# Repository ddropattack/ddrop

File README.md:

# DDRop: Active Memory Interposer Attacks on Confidential VMs by Dropping DDR5 Writes

This repository contains the hardware designs, firmware, host evaluation tools, and attack proof-of-concepts for [**DDRop**](https://ddropattack.eu/ddrop.pdf).

* **Authors:** Jesse De Meulemeester (KU Leuven), Stefan Gloor (ETH Zurich), Patrick Jattke (ETH Zurich), Daniel Moghimi (Google), David Oswald (Durham University), Martin Thompson (Durham University & ZF Automotive UK Ltd), Kaveh Razavi (ETH Zurich), Ingrid Verbauwhede (KU Leuven), and Jo Van Bulck (KU Leuven)

---

## Overview

Modern Trusted Execution Environments (TEEs) such as Intel TDX, Intel Scalable SGX, and AMD SEV-SNP rely on memory encryption to protect enclaves and confidential VMs from an untrusted hypervisor or cloud operator. However, to maintain memory performance, scalable cloud TEEs omit cryptographic freshness guarantees.

DDRop demonstrates active physical interposition attacks on DDR5 at native bus speeds using a custom low-cost DDR5 RDIMM interposer. By injecting parity errors on DDR5 command/address lines, the interposer silently discards cache line writebacks (dropping writes) or swaps chip selects. This repository contains the full materials to inspect, build, and evaluate the interposer hardware, controller firmware, host primitives, and confidential VM attacks.

---

## Repository Structure & Paper Mapping

The contents of this repository correspond directly to the sections of the paper:

| Directory | Paper Section | Description |
|:---|:---|:---|
| [`rdimm-interposer/`](./rdimm-interposer/) | §4.1 | DDR5 RDIMM interposer PCB designs |
| [`rdimm-injection-controller/`](./rdimm-injection-controller/) | §4.1 | Microcontroller injection board designs |
| [`rdimm-injection-controller-firmware/`](./rdimm-injection-controller-firmware/) | §4.1 | Teensy 4.1 firmware & Python control scripts |
| [`host-evaluation/`](./host-evaluation/) | §4.2 | Bare-metal host evaluation of DDRop primitives | 
| [`sev-attacks/`](./sev-attacks/) | §5.1, §5.2.1 | Attacks on AMD SEV-SNP |
| [`sgx-attacks/`](./sgx-attacks/) | §5.1 | Attacks on Intel Scalable SGX | 
| [`tdx-attacks/`](./tdx-attacks/) | §5.1, §5.2.1, §5.2.2, §6 | Attacks on Intel TDX | 

Demonstration videos recorded during physical attack execution are available in the respective directories:
* AMD SEV-SNP write drop: [`sev-attacks/drop-write/sev-drop-write.png`](./sev-attacks/drop-write/sev-drop-write.png)
* AMD SEV-SNP `SNP_PAGE_MOVE` exploit: [`sev-attacks/page-move/sev-page-move.webm`](./sev-attacks/page-move/sev-page-move.webm)
* Intel Scalable SGX write drop: [`sgx-attacks/drop-write/sgx-drop-write.mp4`](./sgx-attacks/drop-write/sgx-drop-write.mp4)
* Intel TDX page relocation: [`tdx-attacks/page-relocate/tdx-page-relocate.webm`](./tdx-attacks/page-relocate/tdx-page-relocate.webm)
* Intel TDX debug bit flip: [`tdx-attacks/sept-injection/tdcs-poc.mp4`](./tdx-attacks/sept-injection/tdcs-poc.mp4)

---

## Getting Started

### Hardware and Software Requirements

#### Software & Build Environment
* Linux x86_64 system
* GCC (supporting C11 / C++17) and Make
* Python 3.8+ with `requirements.txt` packages installed
* [KiCad](https://www.kicad.org/) (v9.0 or later) to view PCB schematics and layouts
* [Arduino IDE](https://www.arduino.cc/) or `teensy_loader_cli` with Teensyduino support (for compiling and flashing the controller firmware)

#### Physical Experiment Requirements
End-to-end physical replication of the attacks requires:
1. The manufactured **DDR5 RDIMM Interposer** and **Injection Controller** boards (design files in `rdimm-interposer/` and `rdimm-injection-controller/`).
2. A **Teensy 4.1** microcontroller board connected to the injection controller.
3. Server hardware with DDR5 RDIMM slots supporting the target TEE:
   * **Intel TDX**: 5th/6th Gen Intel Xeon Scalable processor with TDX enabled.
   * **AMD SEV-SNP**: 4th/5th/6th Gen AMD EPYC processor with SEV-SNP enabled.
   * **Intel Scalable SGX**: 4th/5th/6th Gen Intel Xeon Scalable processor with SGX enabled.

When physical interposer hardware is not available, the software components and attack binaries can still be compiled locally, and their execution flow can be cross-referenced with the provided screencasts.

### Building the Artifacts

You can verify and build all host evaluation tools and attack PoCs from the repository root:

```bash
make all
```

This command automatically builds the dependencies and produces:
* **Host evaluation primitives** (`host-evaluation/drop-write`, `swap-ranks`, `drop-read`)
* **AMD SEV-SNP attack binaries** (`sev-attacks/drop-write`, `page-move`, `movepage`)
* **Intel TDX attack binaries** (`tdx-attacks/drop-write`, `page-relocate`, `attacker-td`, `victim-td`)

To remove all built binaries and object files:
```bash
make clean
```

> [!NOTE]
> Building Intel Scalable SGX enclaves (`sgx-attacks/`) requires the Intel SGX SDK and SGX-Step with `LIBSGXSTEP_DIR` set (see [`sgx-attacks/README.md`](sgx-attacks/README.md)). The microcontroller firmware can be compiled with `make firmware` (see [`rdimm-injection-controller-firmware/README.md`](rdimm-injection-controller-firmware/README.md)).

---

## Detailed Instructions

Refer to the individual README files in each folder for specific execution steps, kernel patch instructions, and command-line parameters:
* [`rdimm-interposer/README.md`](rdimm-interposer/README.md): Interposer specifications, stackup, and modification instructions.
* [`rdimm-injection-controller/README.md`](rdimm-injection-controller/README.md): Controller board hardware and assembly.
* [`rdimm-injection-controller-firmware/README.md`](rdimm-injection-controller-firmware/README.md): Firmware flashing and control API.
* [`host-evaluation/README.md`](host-evaluation/README.md): Running host-level write drop, read drop, and rank swapping primitives.
* [`sev-attacks/README.md`](sev-attacks/README.md): AMD SEV-SNP setup and attack steps.
* [`sgx-attacks/README.md`](sgx-attacks/README.md): Intel Scalable SGX driver patches and enclave evaluation.
* [`tdx-attacks/README.md`](tdx-attacks/README.md): Intel TDX kernel/TDXplore patches, page relocation, and SEPT injection attacks.

---

## Citation

If you reference or build upon this work, please cite the paper:

```bibtex
@inproceedings{ddrop26,
  title     = {{DDRop}: Active Memory Interposer Attacks on Confidential {VMs} by Dropping {DDR5} Writes},
  author    = {De Meulemeester, Jesse and Gloor, Stefan and Jattke, Patrick and Moghimi, Daniel and Oswald, David and Thompson, Martin and Razavi, Kaveh and Verbauwhede, Ingrid and Van Bulck, Jo},
  booktitle = {Proceedings of the 2026 {ACM} {SIGSAC} Conference on Computer and Communications Security ({CCS} '26)},
  publisher = {ACM},
  year      = 2026,
}
```

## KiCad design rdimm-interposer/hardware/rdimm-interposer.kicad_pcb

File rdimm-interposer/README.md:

# RDIMM Interposer

This is an RDIMM variant of the [REFault](https://github.com/comsec-group/refault) [DDR5 fault injection interposer](https://github.com/refault-artifacts/fault-injection-interposer).
Like REFault, the RDIMM interposer supports faulting command/address lines (`CA0-6`).
Additionally, the two chip selects (`CS0` and `CS1`) can be swapped.
Unlike UDIMM, RDIMM has `ALERT_n` and `PAR_A` signals.
`ALERT_n` can be disconnected, leading to a suppressed signal.

With a simple hardware modification, it is also possible to entirely disconnect the `CS0` signal at will (without swapping it with `CS1`).

1. Remove the switch for `CS1` (U19).
1. Cut the trace `CS1_A_n_HOST`
1. Connect `CS1_A_n_HOST` to `CS1_A_n_DIMM`
1. Connect A1 (Pin 1) of U19 (which is connected to B1, Pin 3, of U18) to 1.1V.

Now, `CS1` should be permanently connected, while `CS0` is either connected normally, or the DIMM side is connected to +1.1V, depending on the state of `CS_SWAP`.
Even for single-rank DIMMs, `CS1` still needs to be connected for memory training.
This modification should be integrated into the next PCB revision.

The flat-flex connector is electrically compatible to the [REFault injection controller](https://github.com/refault-artifacts/injection-controller),
so only a firmware change is necessary.

## Mechanical
The mechanical dimensions of DDR5 UDIMMs and RDIMMs are specified in [JEDEC MO-329](https://www.jedec.org/system/files/docs/MO-329I.pdf).
Both variants are the same size and both of them have 288 pins.
They only differ by notch position.
See [docs/drawing.pdf](docs/drawing.pdf) for a mechanical drawing.

## PCB
The PCB was designed using KiCAD v9.0.1.

### Stackup
It has 6 layers and is impedance-controlled, as specified by
`JEDEC RDIMM Raw Card C Annex (JESD305-R8-RCC) v2.0`.
See [docs/drawing.pdf](docs/drawing.pdf) for detailed stackup and trace impedance information.

### Order Information
The PCB was ordered at JLCPCB.

| Option | Value |
|--------|-------|
|Base Material| FR-4|
|Layers| 6|
|Dimension| 133.35 mm* 22.51 mm|
|Product Type| Industrial/Consumer electronics|
|Different Design| 1|
|Delivery Format| Single PCB|
|PCB Thickness| 1.2mm|
|Specify Stackup| yes JLC06121H-1080|
|PCB Color| Green|
|Silkscreen| White|
|Material Type| FR-4 TG155|
|Via Covering| Epoxy Filled & Capped|
|Surface Finish| ENIG|
|Gold Thickness| 2U"|
|Deburring/Edge rounding| Yes|
|Outer Copper Weight| 1 oz|
|Inner Copper Weight| 0.5 oz|
|Gold Fingers| No|
|Electrical Test| Flying Probe Fully Test|
|Castellated Holes| no|
|Press-Fit Hole| No|
|Edge Plating| No|
|Mark on PCB| Order Number|
|Blind Slot| No|
|Min via hole size/diameter| 0.15mm/(0.25/0.3mm)|
|4-Wire Kelvin Test| Yes|
|Paper between PCBs| No|
|Appearance Quality| IPC Class 2 Standard|
|Confirm Production file| No|
|Silkscreen Technology| Ink-jet/Screen Printing Silkscreen|
|Package Box| With JLCPCB logo|
|Inspection Report| No|
|Board Outline Tolerance| ±0.2mm(Regular)|

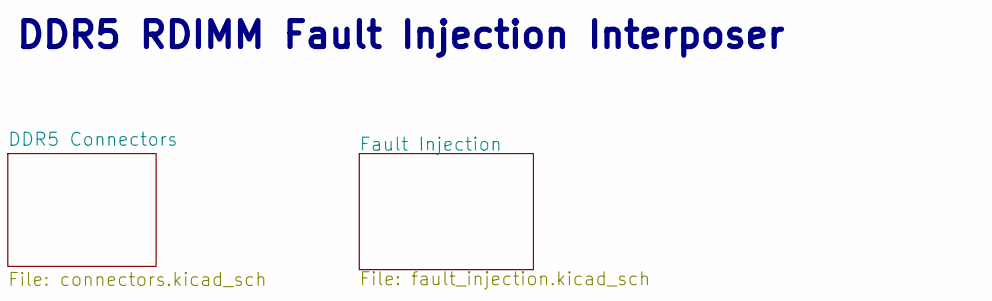
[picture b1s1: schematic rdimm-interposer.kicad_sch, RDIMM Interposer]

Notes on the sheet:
DDR5 RDIMM Fault Injection Interposer

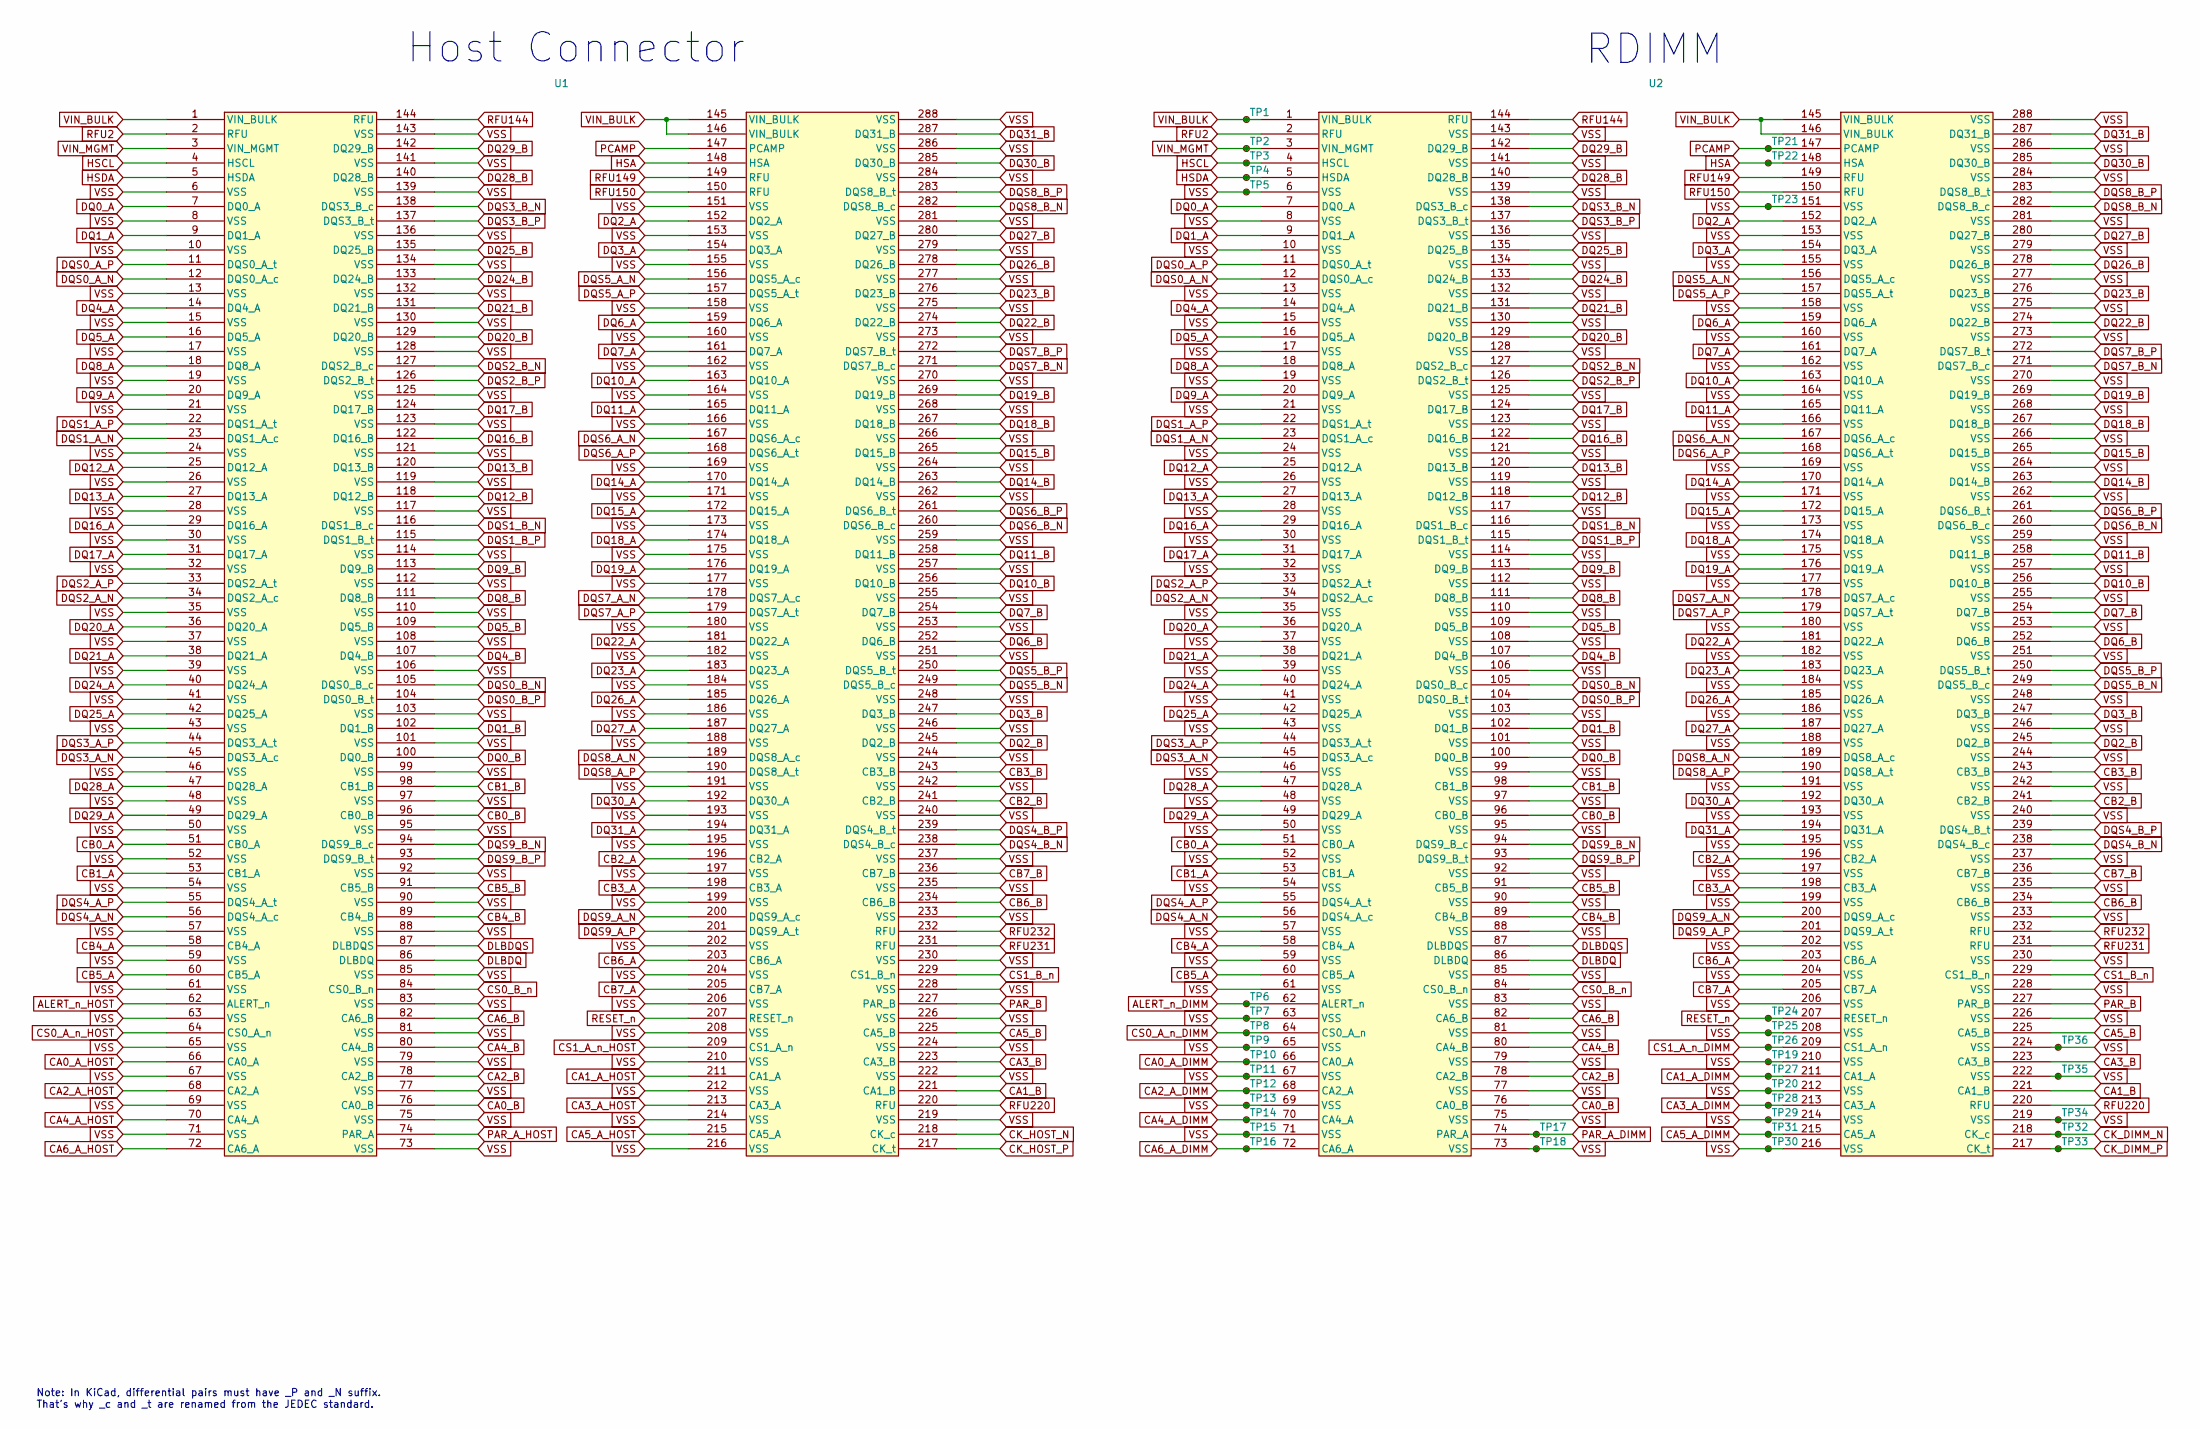
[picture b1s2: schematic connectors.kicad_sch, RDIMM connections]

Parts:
TP1: VIN_BULK; testpoint_small
TP2: VIN_MGMT; testpoint
TP3: HSCL; testpoint
TP4: HSDA; testpoint
TP5, TP7, TP9, TP11, TP13, TP15, TP18, TP19, TP20, TP25, TP29, TP30, TP34, TP35, TP36: VSS; testpoint_small
TP6: ALERT; testpoint
TP8: CS0; testpoint
TP10: CA0; testpoint
TP12: CA2; testpoint
TP14: CA4; testpoint
TP16: CA6; testpoint
TP17: PAR; testpoint
TP21: PCAMP; testpoint
TP22: HSA; testpoint
TP23: TestPoint_Small; testpoint_small
TP24: RESET; testpoint
TP26: CS1; testpoint
TP27: CA1; testpoint
TP28: CA3; testpoint
TP31: CA5; testpoint
TP32: CK_c; testpoint
TP33: CK_t; testpoint
U1: ddr5_edge_connector
U2: ddr5_bottom_conn_double

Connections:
ALERT_n_DIMM: TP6.1, U2.62 (ALERT_n); also elsewhere on the board
ALERT_n_HOST: U1.62 (ALERT_n); also elsewhere on the board
CA0_A_DIMM: TP10.1, U2.66 (CA0_A); also elsewhere on the board
CA0_A_HOST: U1.66 (CA0_A); also elsewhere on the board
CA0_B: U1.76 (CA0_B), U2.76 (CA0_B)
CA1_A_DIMM: TP27.1, U2.211 (CA1_A); also elsewhere on the board
CA1_A_HOST: U1.211 (CA1_A); also elsewhere on the board
CA1_B: U1.221 (CA1_B), U2.221 (CA1_B)
CA2_A_DIMM: TP12.1, U2.68 (CA2_A); also elsewhere on the board
CA2_A_HOST: U1.68 (CA2_A); also elsewhere on the board
CA2_B: U1.78 (CA2_B), U2.78 (CA2_B)
CA3_A_DIMM: TP28.1, U2.213 (CA3_A); also elsewhere on the board
CA3_A_HOST: U1.213 (CA3_A); also elsewhere on the board
CA3_B: U1.223 (CA3_B), U2.223 (CA3_B)
CA4_A_DIMM: TP14.1, U2.70 (CA4_A); also elsewhere on the board
CA4_A_HOST: U1.70 (CA4_A); also elsewhere on the board
CA4_B: U1.80 (CA4_B), U2.80 (CA4_B)
CA5_A_DIMM: TP31.1, U2.215 (CA5_A); also elsewhere on the board
CA5_A_HOST: U1.215 (CA5_A); also elsewhere on the board
CA5_B: U1.225 (CA5_B), U2.225 (CA5_B)
CA6_A_DIMM: TP16.1, U2.72 (CA6_A); also elsewhere on the board
CA6_A_HOST: U1.72 (CA6_A); also elsewhere on the board
CA6_B: U1.82 (CA6_B), U2.82 (CA6_B)
CB0_A: U1.51 (CB0_A), U2.51 (CB0_A)
CB0_B: U1.96 (CB0_B), U2.96 (CB0_B)
CB1_A: U1.53 (CB1_A), U2.53 (CB1_A)
CB1_B: U1.98 (CB1_B), U2.98 (CB1_B)
CB2_A: U1.196 (CB2_A), U2.196 (CB2_A)
CB2_B: U1.241 (CB2_B), U2.241 (CB2_B)
CB3_A: U1.198 (CB3_A), U2.198 (CB3_A)
CB3_B: U1.243 (CB3_B), U2.243 (CB3_B)
CB4_A: U1.58 (CB4_A), U2.58 (CB4_A)
CB4_B: U1.89 (CB4_B), U2.89 (CB4_B)
CB5_A: U1.60 (CB5_A), U2.60 (CB5_A)
CB5_B: U1.91 (CB5_B), U2.91 (CB5_B)
CB6_A: U1.203 (CB6_A), U2.203 (CB6_A)
CB6_B: U1.234 (CB6_B), U2.234 (CB6_B)
CB7_A: U1.205 (CB7_A), U2.205 (CB7_A)
CB7_B: U1.236 (CB7_B), U2.236 (CB7_B)
CK_DIMM_N: TP32.1, U2.218 (CK_c); also elsewhere on the board
CK_DIMM_P: TP33.1, U2.217 (CK_t); also elsewhere on the board
CK_HOST_N: U1.218 (CK_c); also elsewhere on the board
CK_HOST_P: U1.217 (CK_t); also elsewhere on the board
CS0_A_n_DIMM: TP8.1, U2.64 (CS0_A_n); also elsewhere on the board
CS0_A_n_HOST: U1.64 (CS0_A_n); also elsewhere on the board
CS0_B_n: U1.84 (CS0_B_n), U2.84 (CS0_B_n)
CS1_A_n_DIMM: TP26.1, U2.209 (CS1_A_n); also elsewhere on the board
CS1_A_n_HOST: U1.209 (CS1_A_n); also elsewhere on the board
CS1_B_n: U1.229 (CS1_B_n), U2.229 (CS1_B_n)
DLBDQ: U1.86 (DLBDQ), U2.86 (DLBDQ)
DLBDQS: U1.87 (DLBDQS), U2.87 (DLBDQS)
DQ0_A: U1.7 (DQ0_A), U2.7 (DQ0_A)
DQ0_B: U1.100 (DQ0_B), U2.100 (DQ0_B)
DQ1_A: U1.9 (DQ1_A), U2.9 (DQ1_A)
DQ1_B: U1.102 (DQ1_B), U2.102 (DQ1_B)
DQ2_A: U1.152 (DQ2_A), U2.152 (DQ2_A)
DQ2_B: U1.245 (DQ2_B), U2.245 (DQ2_B)
DQ3_A: U1.154 (DQ3_A), U2.154 (DQ3_A)
DQ3_B: U1.247 (DQ3_B), U2.247 (DQ3_B)
DQ4_A: U1.14 (DQ4_A), U2.14 (DQ4_A)
DQ4_B: U1.107 (DQ4_B), U2.107 (DQ4_B)
DQ5_A: U1.16 (DQ5_A), U2.16 (DQ5_A)
DQ5_B: U1.109 (DQ5_B), U2.109 (DQ5_B)
DQ6_A: U1.159 (DQ6_A), U2.159 (DQ6_A)
DQ6_B: U1.252 (DQ6_B), U2.252 (DQ6_B)
DQ7_A: U1.161 (DQ7_A), U2.161 (DQ7_A)
DQ7_B: U1.254 (DQ7_B), U2.254 (DQ7_B)
DQ8_A: U1.18 (DQ8_A), U2.18 (DQ8_A)
DQ8_B: U1.111 (DQ8_B), U2.111 (DQ8_B)
DQ9_A: U1.20 (DQ9_A), U2.20 (DQ9_A)
DQ9_B: U1.113 (DQ9_B), U2.113 (DQ9_B)
DQ10_A: U1.163 (DQ10_A), U2.163 (DQ10_A)
DQ10_B: U1.256 (DQ10_B), U2.256 (DQ10_B)
DQ11_A: U1.165 (DQ11_A), U2.165 (DQ11_A)
DQ11_B: U1.258 (DQ11_B), U2.258 (DQ11_B)
DQ12_A: U1.25 (DQ12_A), U2.25 (DQ12_A)
DQ12_B: U1.118 (DQ12_B), U2.118 (DQ12_B)
DQ13_A: U1.27 (DQ13_A), U2.27 (DQ13_A)
DQ13_B: U1.120 (DQ13_B), U2.120 (DQ13_B)
DQ14_A: U1.170 (DQ14_A), U2.170 (DQ14_A)
DQ14_B: U1.263 (DQ14_B), U2.263 (DQ14_B)
DQ15_A: U1.172 (DQ15_A), U2.172 (DQ15_A)
DQ15_B: U1.265 (DQ15_B), U2.265 (DQ15_B)
DQ16_A: U1.29 (DQ16_A), U2.29 (DQ16_A)
DQ16_B: U1.122 (DQ16_B), U2.122 (DQ16_B)
DQ17_A: U1.31 (DQ17_A), U2.31 (DQ17_A)
DQ17_B: U1.124 (DQ17_B), U2.124 (DQ17_B)
DQ18_A: U1.174 (DQ18_A), U2.174 (DQ18_A)
DQ18_B: U1.267 (DQ18_B), U2.267 (DQ18_B)
DQ19_A: U1.176 (DQ19_A), U2.176 (DQ19_A)
DQ19_B: U1.269 (DQ19_B), U2.269 (DQ19_B)
DQ20_A: U1.36 (DQ20_A), U2.36 (DQ20_A)
DQ20_B: U1.129 (DQ20_B), U2.129 (DQ20_B)
DQ21_A: U1.38 (DQ21_A), U2.38 (DQ21_A)
DQ21_B: U1.131 (DQ21_B), U2.131 (DQ21_B)
DQ22_A: U1.181 (DQ22_A), U2.181 (DQ22_A)
DQ22_B: U1.274 (DQ22_B), U2.274 (DQ22_B)
DQ23_A: U1.183 (DQ23_A), U2.183 (DQ23_A)
DQ23_B: U1.276 (DQ23_B), U2.276 (DQ23_B)
DQ24_A: U1.40 (DQ24_A), U2.40 (DQ24_A)
DQ24_B: U1.133 (DQ24_B), U2.133 (DQ24_B)
DQ25_A: U1.42 (DQ25_A), U2.42 (DQ25_A)
DQ25_B: U1.135 (DQ25_B), U2.135 (DQ25_B)
DQ26_A: U1.185 (DQ26_A), U2.185 (DQ26_A)
DQ26_B: U1.278 (DQ26_B), U2.278 (DQ26_B)
DQ27_A: U1.187 (DQ27_A), U2.187 (DQ27_A)
DQ27_B: U1.280 (DQ27_B), U2.280 (DQ27_B)
DQ28_A: U1.47 (DQ28_A), U2.47 (DQ28_A)
DQ28_B: U1.140 (DQ28_B), U2.140 (DQ28_B)
DQ29_A: U1.49 (DQ29_A), U2.49 (DQ29_A)
DQ29_B: U1.142 (DQ29_B), U2.142 (DQ29_B)
DQ30_A: U1.192 (DQ30_A), U2.192 (DQ30_A)
DQ30_B: U1.285 (DQ30_B), U2.285 (DQ30_B)
DQ31_A: U1.194 (DQ31_A), U2.194 (DQ31_A)
DQ31_B: U1.287 (DQ31_B), U2.287 (DQ31_B)
DQS0_A_N: U1.12 (DQS0_A_c), U2.12 (DQS0_A_c)
DQS0_A_P: U1.11 (DQS0_A_t), U2.11 (DQS0_A_t)
DQS0_B_N: U1.105 (DQS0_B_c), U2.105 (DQS0_B_c)
DQS0_B_P: U1.104 (DQS0_B_t), U2.104 (DQS0_B_t)
DQS1_A_N: U1.23 (DQS1_A_c), U2.23 (DQS1_A_c)
DQS1_A_P: U1.22 (DQS1_A_t), U2.22 (DQS1_A_t)
DQS1_B_N: U1.116 (DQS1_B_c), U2.116 (DQS1_B_c)
DQS1_B_P: U1.115 (DQS1_B_t), U2.115 (DQS1_B_t)
DQS2_A_N: U1.34 (DQS2_A_c), U2.34 (DQS2_A_c)
DQS2_A_P: U1.33 (DQS2_A_t), U2.33 (DQS2_A_t)
DQS2_B_N: U1.127 (DQS2_B_c), U2.127 (DQS2_B_c)
DQS2_B_P: U1.126 (DQS2_B_t), U2.126 (DQS2_B_t)
DQS3_A_N: U1.45 (DQS3_A_c), U2.45 (DQS3_A_c)
DQS3_A_P: U1.44 (DQS3_A_t), U2.44 (DQS3_A_t)
DQS3_B_N: U1.138 (DQS3_B_c), U2.138 (DQS3_B_c)
DQS3_B_P: U1.137 (DQS3_B_t), U2.137 (DQS3_B_t)
DQS4_A_N: U1.56 (DQS4_A_c), U2.56 (DQS4_A_c)
DQS4_A_P: U1.55 (DQS4_A_t), U2.55 (DQS4_A_t)
DQS4_B_N: U1.238 (DQS4_B_c), U2.238 (DQS4_B_c)
DQS4_B_P: U1.239 (DQS4_B_t), U2.239 (DQS4_B_t)
DQS5_A_N: U1.156 (DQS5_A_c), U2.156 (DQS5_A_c)
DQS5_A_P: U1.157 (DQS5_A_t), U2.157 (DQS5_A_t)
DQS5_B_N: U1.249 (DQS5_B_c), U2.249 (DQS5_B_c)
DQS5_B_P: U1.250 (DQS5_B_t), U2.250 (DQS5_B_t)
DQS6_A_N: U1.167 (DQS6_A_c), U2.167 (DQS6_A_c)
DQS6_A_P: U1.168 (DQS6_A_t), U2.168 (DQS6_A_t)
DQS6_B_N: U1.260 (DQS6_B_c), U2.260 (DQS6_B_c)
DQS6_B_P: U1.261 (DQS6_B_t), U2.261 (DQS6_B_t)
DQS7_A_N: U1.178 (DQS7_A_c), U2.178 (DQS7_A_c)
DQS7_A_P: U1.179 (DQS7_A_t), U2.179 (DQS7_A_t)
DQS7_B_N: U1.271 (DQS7_B_c), U2.271 (DQS7_B_c)
DQS7_B_P: U1.272 (DQS7_B_t), U2.272 (DQS7_B_t)
DQS8_A_N: U1.189 (DQS8_A_c), U2.189 (DQS8_A_c)
DQS8_A_P: U1.190 (DQS8_A_t), U2.190 (DQS8_A_t)
DQS8_B_N: U1.282 (DQS8_B_c), U2.282 (DQS8_B_c)
DQS8_B_P: U1.283 (DQS8_B_t), U2.283 (DQS8_B_t)
DQS9_A_N: U1.200 (DQS9_A_c), U2.200 (DQS9_A_c)
DQS9_A_P: U1.201 (DQS9_A_t), U2.201 (DQS9_A_t)
DQS9_B_N: U1.94 (DQS9_B_c), U2.94 (DQS9_B_c)
DQS9_B_P: U1.93 (DQS9_B_t), U2.93 (DQS9_B_t)
HSA: TP22.1, U1.148 (HSA), U2.148 (HSA)
HSCL: TP3.1, U1.4 (HSCL), U2.4 (HSCL)
HSDA: TP4.1, U1.5 (HSDA), U2.5 (HSDA)
PAR_A_DIMM: TP17.1, U2.74 (PAR_A); also elsewhere on the board
PAR_A_HOST: U1.74 (PAR_A); also elsewhere on the board
PAR_B: U1.227 (PAR_B), U2.227 (PAR_B)
PCAMP: TP21.1, U1.147 (PCAMP), U2.147 (PCAMP)
RESET_n: TP24.1, U1.207 (RESET_n), U2.207 (RESET_n)
RFU2: U1.2 (RFU), U2.2 (RFU)
RFU144: U1.144 (RFU), U2.144 (RFU)
RFU149: U1.149 (RFU), U2.149 (RFU)
RFU150: U1.150 (RFU), U2.150 (RFU)
RFU220: U1.220 (RFU), U2.220 (RFU)
RFU231: U1.231 (RFU), U2.231 (RFU)
RFU232: U1.232 (RFU), U2.232 (RFU)
VIN_BULK: TP1.1, U1.1 (VIN_BULK), U1.145 (VIN_BULK), U1.146 (VIN_BULK), U2.1 (VIN_BULK), U2.145 (VIN_BULK), U2.146 (VIN_BULK)
VIN_MGMT: TP2.1, U1.3 (VIN_MGMT), U2.3 (VIN_MGMT)
VSS: TP5.1, TP7.1, TP9.1, TP11.1, TP13.1, TP15.1, TP18.1, TP19.1, TP20.1, TP23.1, TP25.1, TP29.1, TP30.1, TP34.1, TP35.1, TP36.1, U1.6 (VSS), U1.8 (VSS), U1.10 (VSS), U1.13 (VSS), U1.15 (VSS), U1.17 (VSS), U1.19 (VSS), U1.21 (VSS), U1.24 (VSS), U1.26 (VSS), U1.28 (VSS), U1.30 (VSS), U1.32 (VSS), U1.35 (VSS), U1.37 (VSS), U1.39 (VSS), U1.41 (VSS), U1.43 (VSS), U1.46 (VSS), U1.48 (VSS), U1.50 (VSS), U1.52 (VSS), U1.54 (VSS), U1.57 (VSS), U1.59 (VSS), U1.61 (VSS), U1.63 (VSS), U1.65 (VSS), U1.67 (VSS), U1.69 (VSS), U1.71 (VSS), U1.73 (VSS), U1.75 (VSS), U1.77 (VSS), U1.79 (VSS), U1.81 (VSS), U1.83 (VSS), U1.85 (VSS), U1.88 (VSS), U1.90 (VSS), U1.92 (VSS), U1.95 (VSS), U1.97 (VSS), U1.99 (VSS), U1.101 (VSS), U1.103 (VSS), U1.106 (VSS), U1.108 (VSS), U1.110 (VSS), U1.112 (VSS), U1.114 (VSS), U1.117 (VSS), U1.119 (VSS), U1.121 (VSS), U1.123 (VSS), U1.125 (VSS), U1.128 (VSS), U1.130 (VSS), U1.132 (VSS), U1.134 (VSS), U1.136 (VSS), U1.139 (VSS), U1.141 (VSS), U1.143 (VSS), U1.151 (VSS), U1.153 (VSS), U1.155 (VSS), U1.158 (VSS), U1.160 (VSS), U1.162 (VSS), U1.164 (VSS), U1.166 (VSS), U1.169 (VSS), U1.171 (VSS), U1.173 (VSS), U1.175 (VSS), U1.177 (VSS), U1.180 (VSS), U1.182 (VSS), U1.184 (VSS), U1.186 (VSS), U1.188 (VSS), U1.191 (VSS), U1.193 (VSS), U1.195 (VSS), U1.197 (VSS), U1.199 (VSS), U1.202 (VSS), U1.204 (VSS), U1.206 (VSS), U1.208 (VSS), U1.210 (VSS), U1.212 (VSS), U1.214 (VSS), U1.216 (VSS), U1.219 (VSS), U1.222 (VSS), U1.224 (VSS), U1.226 (VSS), U1.228 (VSS), U1.230 (VSS), U1.233 (VSS), U1.235 (VSS), U1.237 (VSS), U1.240 (VSS), U1.242 (VSS), U1.244 (VSS), U1.246 (VSS), U1.248 (VSS), U1.251 (VSS), U1.253 (VSS), U1.255 (VSS), U1.257 (VSS), U1.259 (VSS), U1.262 (VSS), U1.264 (VSS), U1.266 (VSS), U1.268 (VSS), U1.270 (VSS), U1.273 (VSS), U1.275 (VSS), U1.277 (VSS), U1.279 (VSS), U1.281 (VSS), U1.284 (VSS), U1.286 (VSS), U1.288 (VSS), U2.6 (VSS), U2.8 (VSS), U2.10 (VSS), U2.13 (VSS), U2.15 (VSS), U2.17 (VSS), U2.19 (VSS), U2.21 (VSS), U2.24 (VSS), U2.26 (VSS), U2.28 (VSS), U2.30 (VSS), U2.32 (VSS), U2.35 (VSS), U2.37 (VSS), U2.39 (VSS), U2.41 (VSS), U2.43 (VSS), U2.46 (VSS), U2.48 (VSS), U2.50 (VSS), U2.52 (VSS), U2.54 (VSS), U2.57 (VSS), U2.59 (VSS), U2.61 (VSS), U2.63 (VSS), U2.65 (VSS), U2.67 (VSS), U2.69 (VSS), U2.71 (VSS), U2.73 (VSS), U2.75 (VSS), U2.77 (VSS), U2.79 (VSS), U2.81 (VSS), U2.83 (VSS), U2.85 (VSS), U2.88 (VSS), U2.90 (VSS), U2.92 (VSS), U2.95 (VSS), U2.97 (VSS), U2.99 (VSS), U2.101 (VSS), U2.103 (VSS), U2.106 (VSS), U2.108 (VSS), U2.110 (VSS), U2.112 (VSS), U2.114 (VSS), U2.117 (VSS), U2.119 (VSS), U2.121 (VSS), U2.123 (VSS), U2.125 (VSS), U2.128 (VSS), U2.130 (VSS), U2.132 (VSS), U2.134 (VSS), U2.136 (VSS), U2.139 (VSS), U2.141 (VSS), U2.143 (VSS), U2.151 (VSS), U2.153 (VSS), U2.155 (VSS), U2.158 (VSS), U2.160 (VSS), U2.162 (VSS), U2.164 (VSS), U2.166 (VSS), U2.169 (VSS), U2.171 (VSS), U2.173 (VSS), U2.175 (VSS), U2.177 (VSS), U2.180 (VSS), U2.182 (VSS), U2.184 (VSS), U2.186 (VSS), U2.188 (VSS), U2.191 (VSS), U2.193 (VSS), U2.195 (VSS), U2.197 (VSS), U2.199 (VSS), U2.202 (VSS), U2.204 (VSS), U2.206 (VSS), U2.208 (VSS), U2.210 (VSS), U2.212 (VSS), U2.214 (VSS), U2.216 (VSS), U2.219 (VSS), U2.222 (VSS), U2.224 (VSS), U2.226 (VSS), U2.228 (VSS), U2.230 (VSS), U2.233 (VSS), U2.235 (VSS), U2.237 (VSS), U2.240 (VSS), U2.242 (VSS), U2.244 (VSS), U2.246 (VSS), U2.248 (VSS), U2.251 (VSS), U2.253 (VSS), U2.255 (VSS), U2.257 (VSS), U2.259 (VSS), U2.262 (VSS), U2.264 (VSS), U2.266 (VSS), U2.268 (VSS), U2.270 (VSS), U2.273 (VSS), U2.275 (VSS), U2.277 (VSS), U2.279 (VSS), U2.281 (VSS), U2.284 (VSS), U2.286 (VSS), U2.288 (VSS); also elsewhere on the board

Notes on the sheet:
RDIMM
Host Connector
Note: In KiCad, differential pairs must have _P and _N suffix. That's why _c and _t are renamed from the JEDEC standard.

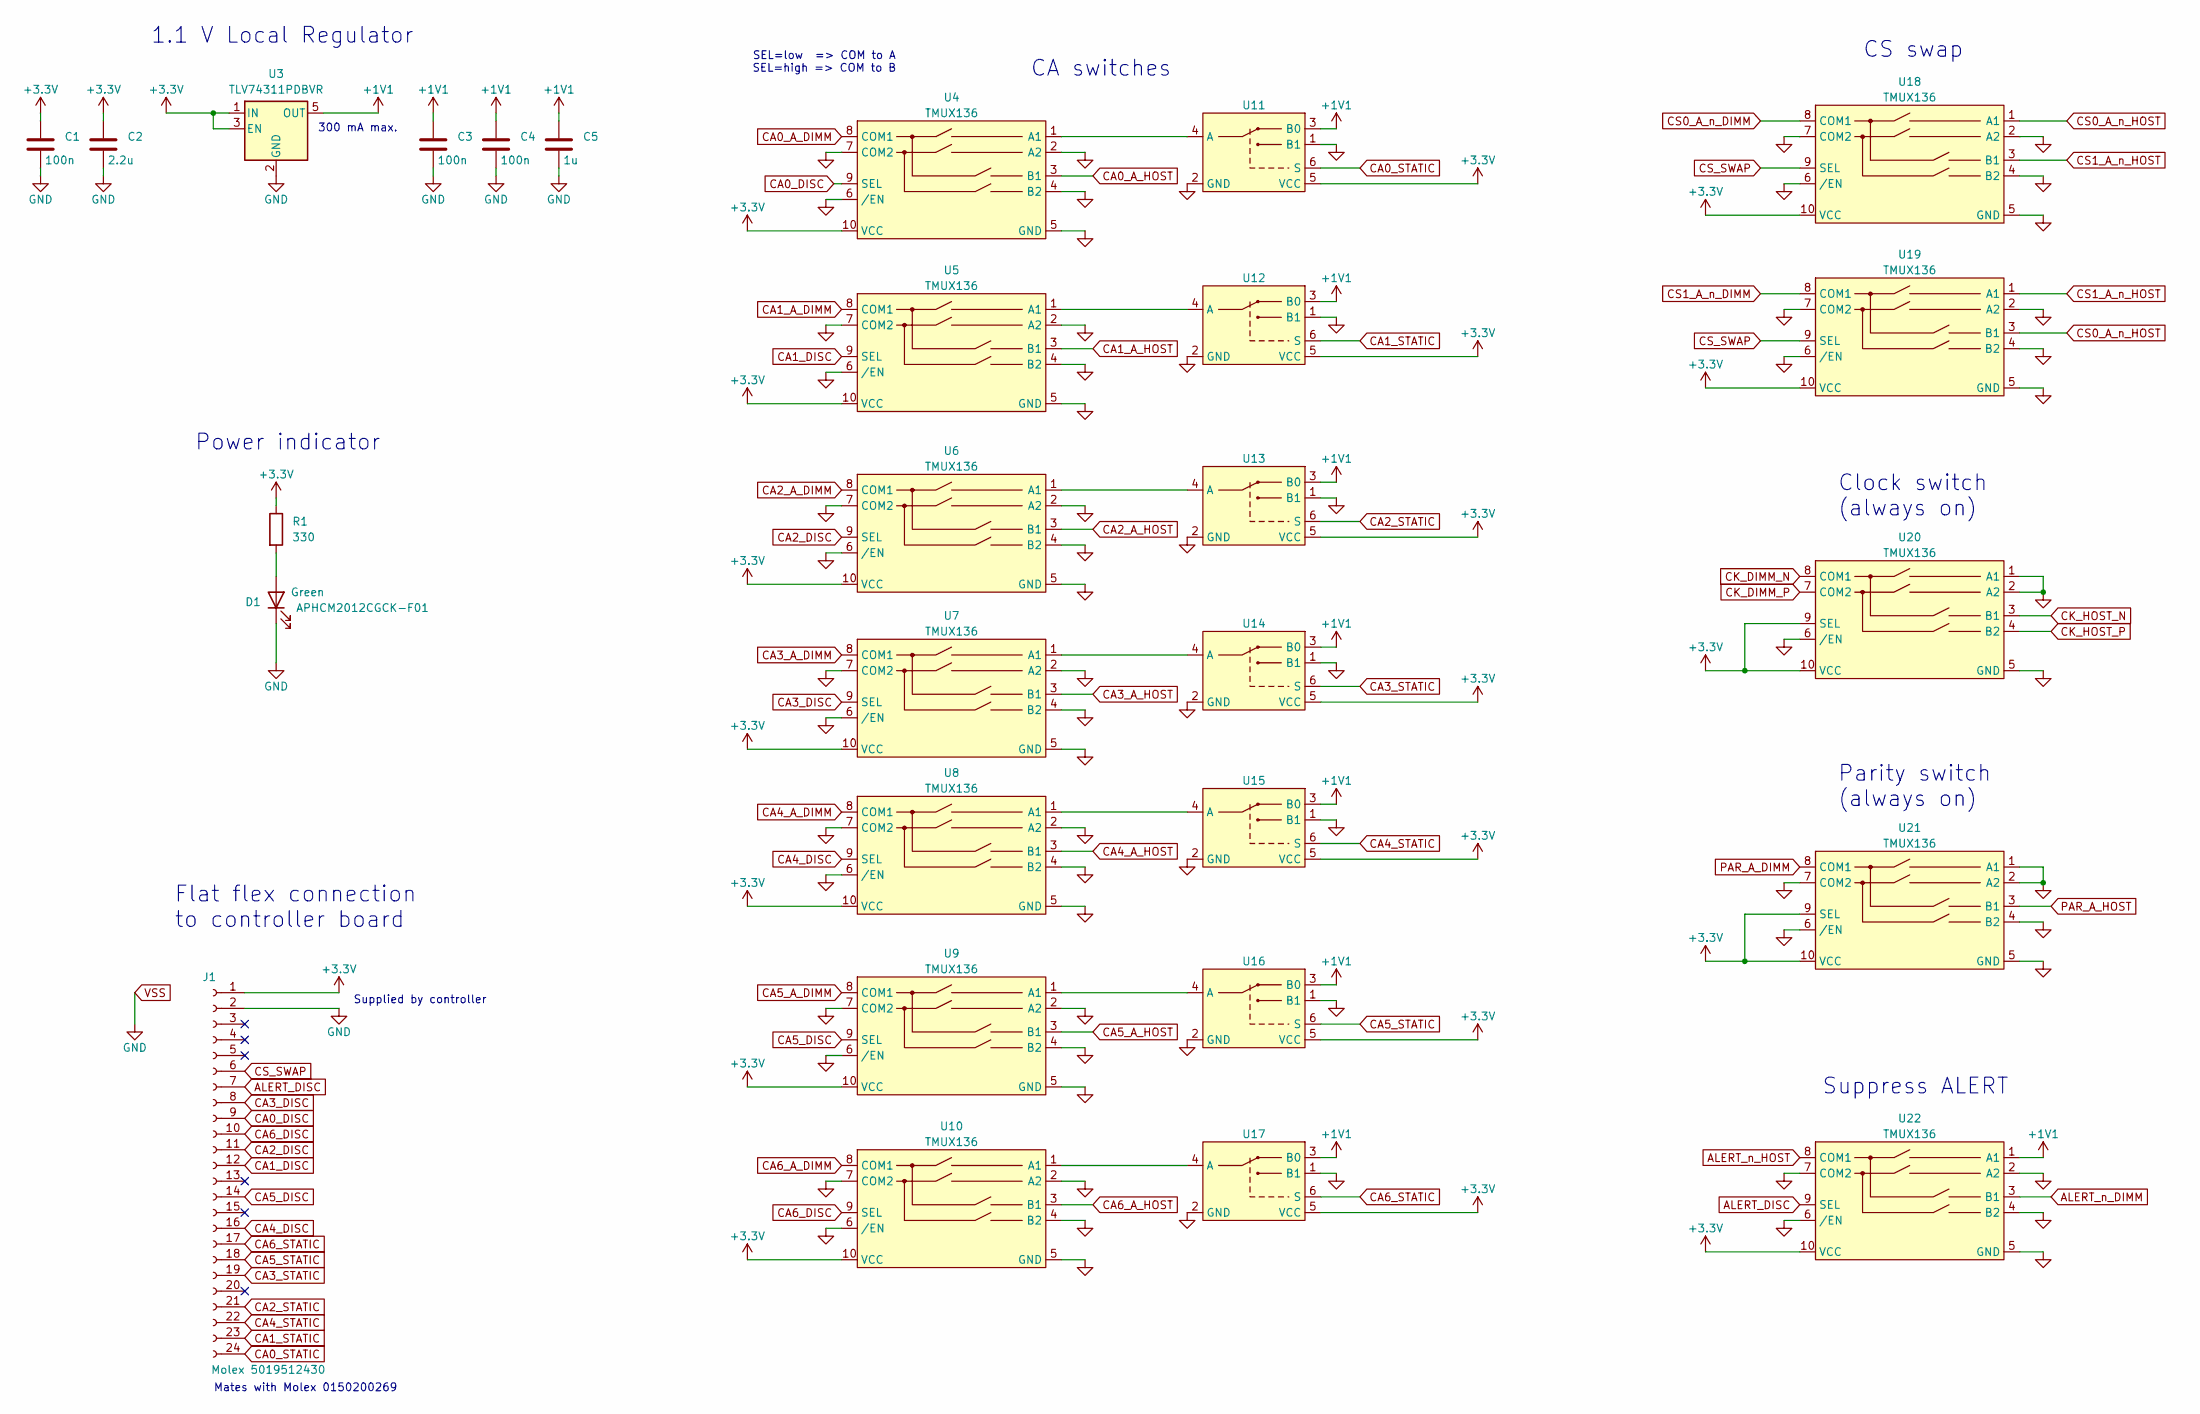
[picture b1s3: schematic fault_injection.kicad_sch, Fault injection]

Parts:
C1, C3, C4: 100n; C_0603_1608Metric
C2: 2.2u; C_0603_1608Metric
C5: 1u; C_0603_1608Metric
D1: APHCM2012CGCK-F01; LED_0805_2012Metric
J1: Molex 5019512430; 5019512430
R1: 330; R_0603_1608Metric
U3: TLV74311PDBVR; SOT-23-5
U4, U5, U6, U7, U8, U9, U10, U18, U19, U20, U21, U22: TMUX136; uqfn10
U11, U12, U13, U14, U15, U16, U17: SOT-363_SC-70-6

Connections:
+1V1: C3.1, C4.1, C5.1, U3.5 (OUT), U11.3 (B0), U12.3 (B0), U13.3 (B0), U14.3 (B0), U15.3 (B0), U16.3 (B0), U17.3 (B0), U22.1 (A1)
+3.3V: C1.1, C2.1, J1.1, R1.1, U3.1 (IN), U3.3 (EN), U4.10 (VCC), U5.10 (VCC), U6.10 (VCC), U7.10 (VCC), U8.10 (VCC), U9.10 (VCC), U10.10 (VCC), U11.5 (VCC), U12.5 (VCC), U13.5 (VCC), U14.5 (VCC), U15.5 (VCC), U16.5 (VCC), U17.5 (VCC), U18.10 (VCC), U19.10 (VCC), U20.9 (SEL), U20.10 (VCC), U21.9 (SEL), U21.10 (VCC), U22.10 (VCC)
ALERT_DISC: J1.7, U22.9 (SEL)
ALERT_n_DIMM: U22.3 (B1); also elsewhere on the board
ALERT_n_HOST: U22.8 (COM1); also elsewhere on the board
CA0_A_DIMM: U4.8 (COM1); also elsewhere on the board
CA0_A_HOST: U4.3 (B1); also elsewhere on the board
CA0_DISC: J1.9, U4.9 (SEL)
CA0_STATIC: J1.24, U11.6 (S)
CA1_A_DIMM: U5.8 (COM1); also elsewhere on the board
CA1_A_HOST: U5.3 (B1); also elsewhere on the board
CA1_DISC: J1.12, U5.9 (SEL)
CA1_STATIC: J1.23, U12.6 (S)
CA2_A_DIMM: U6.8 (COM1); also elsewhere on the board
CA2_A_HOST: U6.3 (B1); also elsewhere on the board
CA2_DISC: J1.11, U6.9 (SEL)
CA2_STATIC: J1.21, U13.6 (S)
CA3_A_DIMM: U7.8 (COM1); also elsewhere on the board
CA3_A_HOST: U7.3 (B1); also elsewhere on the board
CA3_DISC: J1.8, U7.9 (SEL)
CA3_STATIC: J1.19, U14.6 (S)
CA4_A_DIMM: U8.8 (COM1); also elsewhere on the board
CA4_A_HOST: U8.3 (B1); also elsewhere on the board
CA4_DISC: J1.16, U8.9 (SEL)
CA4_STATIC: J1.22, U15.6 (S)
CA5_A_DIMM: U9.8 (COM1); also elsewhere on the board
CA5_A_HOST: U9.3 (B1); also elsewhere on the board
CA5_DISC: J1.14, U9.9 (SEL)
CA5_STATIC: J1.18, U16.6 (S)
CA6_A_DIMM: U10.8 (COM1); also elsewhere on the board
CA6_A_HOST: U10.3 (B1); also elsewhere on the board
CA6_DISC: J1.10, U10.9 (SEL)
CA6_STATIC: J1.17, U17.6 (S)
CK_DIMM_N: U20.8 (COM1); also elsewhere on the board
CK_DIMM_P: U20.7 (COM2); also elsewhere on the board
CK_HOST_N: U20.3 (B1); also elsewhere on the board
CK_HOST_P: U20.4 (B2); also elsewhere on the board
CS0_A_n_DIMM: U18.8 (COM1); also elsewhere on the board
CS0_A_n_HOST: U18.1 (A1), U19.3 (B1); also elsewhere on the board
CS1_A_n_DIMM: U19.8 (COM1); also elsewhere on the board
CS1_A_n_HOST: U18.3 (B1), U19.1 (A1); also elsewhere on the board
CS_SWAP: J1.6, U18.9 (SEL), U19.9 (SEL)
unnamed: D1.2 (A), R1.2
unnamed: U10.1 (A1), U17.4 (A)
unnamed: U4.1 (A1), U11.4 (A)
unnamed: U5.1 (A1), U12.4 (A)
unnamed: U6.1 (A1), U13.4 (A)
unnamed: U7.1 (A1), U14.4 (A)
unnamed: U8.1 (A1), U15.4 (A)
unnamed: U9.1 (A1), U16.4 (A)
PAR_A_DIMM: U21.8 (COM1); also elsewhere on the board
PAR_A_HOST: U21.3 (B1); also elsewhere on the board
VSS: C1.2, C2.2, C3.2, C4.2, C5.2, D1.1 (K), J1.2, U3.2 (GND), U4.2 (A2), U4.4 (B2), U4.5 (GND), U4.6 (/EN), U4.7 (COM2), U5.2 (A2), U5.4 (B2), U5.5 (GND), U5.6 (/EN), U5.7 (COM2), U6.2 (A2), U6.4 (B2), U6.5 (GND), U6.6 (/EN), U6.7 (COM2), U7.2 (A2), U7.4 (B2), U7.5 (GND), U7.6 (/EN), U7.7 (COM2), U8.2 (A2), U8.4 (B2), U8.5 (GND), U8.6 (/EN), U8.7 (COM2), U9.2 (A2), U9.4 (B2), U9.5 (GND), U9.6 (/EN), U9.7 (COM2), U10.2 (A2), U10.4 (B2), U10.5 (GND), U10.6 (/EN), U10.7 (COM2), U11.1 (B1), U11.2 (GND), U12.1 (B1), U12.2 (GND), U13.1 (B1), U13.2 (GND), U14.1 (B1), U14.2 (GND), U15.1 (B1), U15.2 (GND), U16.1 (B1), U16.2 (GND), U17.1 (B1), U17.2 (GND), U18.2 (A2), U18.4 (B2), U18.5 (GND), U18.6 (/EN), U18.7 (COM2), U19.2 (A2), U19.4 (B2), U19.5 (GND), U19.6 (/EN), U19.7 (COM2), U20.1 (A1), U20.2 (A2), U20.5 (GND), U20.6 (/EN), U21.1 (A1), U21.2 (A2), U21.4 (B2), U21.5 (GND), U21.6 (/EN), U21.7 (COM2), U22.2 (A2), U22.4 (B2), U22.5 (GND), U22.6 (/EN), U22.7 (COM2); also elsewhere on the board

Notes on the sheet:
Power indicator
SEL=low => COM to A SEL=high => COM to B
Flat flex connection to controller board
CS swap
Mates with Molex 0150200269
CA switches
Parity switch (always on)
Suppress ALERT
1.1 V Local Regulator
Clock switch (always on)
Supplied by controller
300 mA max.

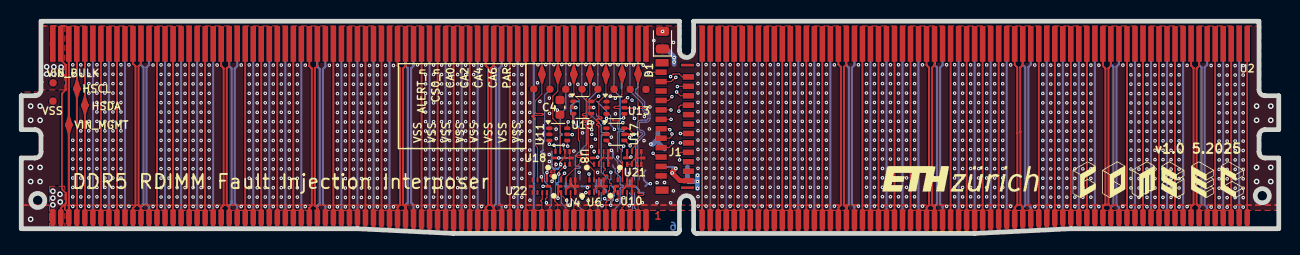
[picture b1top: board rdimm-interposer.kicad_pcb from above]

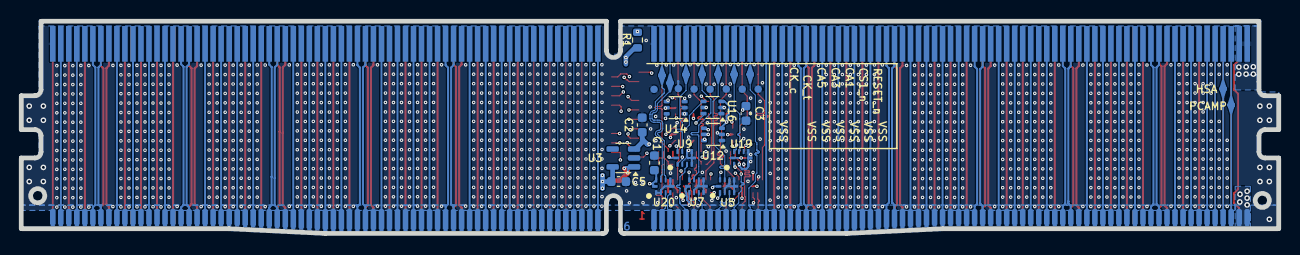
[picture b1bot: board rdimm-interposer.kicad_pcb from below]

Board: 6 copper layers, 133.3 x 22.5 mm, 66 parts (30 on the bottom side), 199 nets.
